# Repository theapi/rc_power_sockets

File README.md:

# RC Power Sockets
Using remote controlled power sockets - http://www.maplin.co.uk/p/remote-controlled-mains-sockets-set-3-pack-n79ka

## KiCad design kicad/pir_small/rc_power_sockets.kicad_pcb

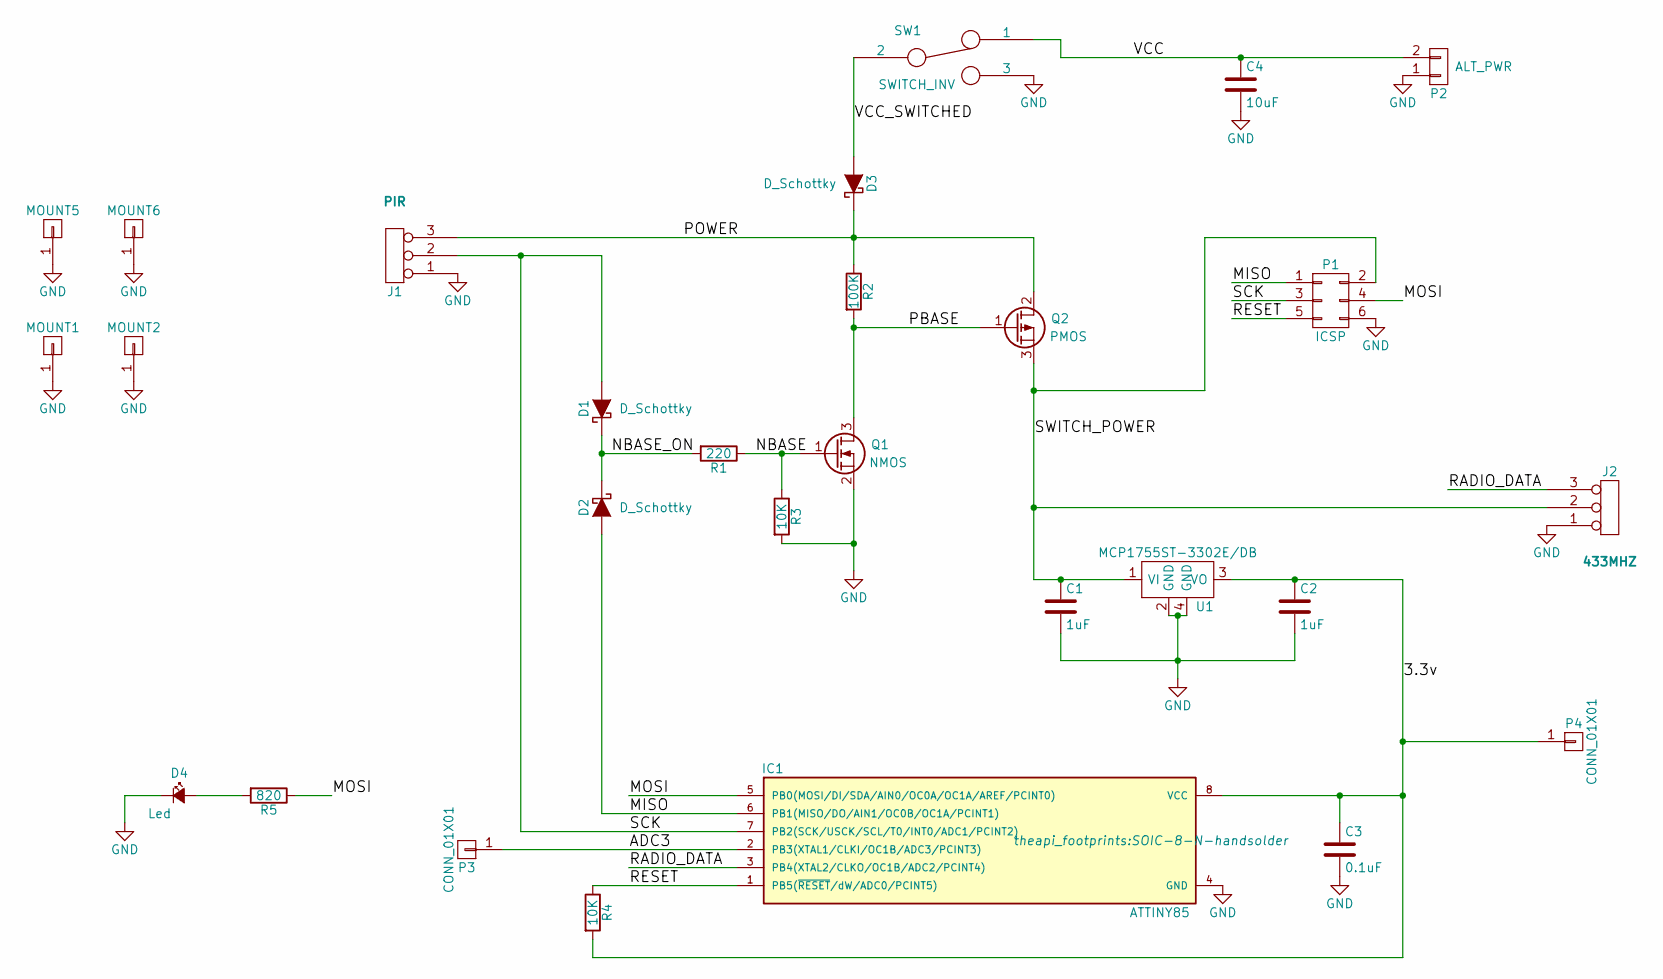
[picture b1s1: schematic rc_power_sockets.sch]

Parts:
C1, C2: 1uF; C_0805_HandSoldering
C3: 0.1uF; C_0805_HandSoldering
C4: 10uF; C_0805_HandSoldering
D1, D2, D3: D_Schottky; SOD-123-handsolder
D4: Led; LED_0805
IC1: ATTINY85; SOIC-8-N-handsolder
J1: PIR; Socket_Strip_Straight_1x03
J2: 433MHZ; Socket_Strip_Straight_1x03
MOUNT1, MOUNT2, MOUNT5, MOUNT6: CONN_01X01; Pin_Header_Straight_1x01
P1: ICSP; Pin_Header_Straight_2x03
P2: ALT_PWR; Pin_Header_Straight_1x02
P3, P4: CONN_01X01; Pin_Header_Straight_1x01
Q1: NMOS; SOT-23_Handsoldering
Q2: PMOS; SOT-23_Handsoldering
R1: 220; R_0805_HandSoldering
R2: 100K; R_0805_HandSoldering
R3, R4: 10K; R_0805_HandSoldering
R5: 820; R_0805_HandSoldering
SW1: SWITCH_INV; SW_Micro_SPST
U1: MCP1755ST-3302E/DB; SOT-223

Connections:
/3.3v: C2.1, C3.1, IC1.8 (VCC), P4.1, R4.2, U1.3 (VO)
/ADC3: IC1.2 (PB3(XTAL1/CLKI/OC1B/ADC3/PCINT3)), P3.1
/MISO: D2.2 (A), IC1.6 (PB1(MISO/DO/AIN1/OC0B/OC1A/PCINT1)), P1.1
/MOSI: IC1.5 (PB0(MOSI/DI/SDA/AIN0/OC0A/OC1A/AREF/PCI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), P1.4, R5.1
/NBASE: Q1.1 (G), R1.1, R3.1
/NBASE_ON: D1.1 (K), D2.1 (K), R1.2
/PBASE: Q1.3 (D), Q2.1 (G), R2.2
/POWER: D3.1 (K), J1.3, Q2.2 (D), R2.1
/RADIO_DATA: IC1.3 (PB4(XTAL2/CLKO/OC1B/ADC2/PCINT4)), J2.3
/RESET: IC1.1 (PB5(~RESET~/dW/ADC0/PCINT5)), P1.5, R4.1
/SCK: D1.2 (A), IC1.7 (PB2(SCK/USCK/SCL/T0/INT0/ADC1/PCINT2)), J1.2, P1.3
/SWITCH_POWER: C1.1, J2.2, P1.2, Q2.3 (S), U1.1 (VI)
/VCC: C4.1, P2.2, SW1.1
/VCC_SWITCHED: D3.2 (A), SW1.2
GND: C1.2, C2.2, C3.2, C4.2, D4.1 (K), IC1.4 (GND), J1.1, J2.1, MOUNT1.1, MOUNT2.1, MOUNT5.1, MOUNT6.1, P1.6, P2.1, Q1.2 (S), R3.2, SW1.3, U1.2 (GND), U1.4 (GND)
unnamed: D4.2 (A), R5.2

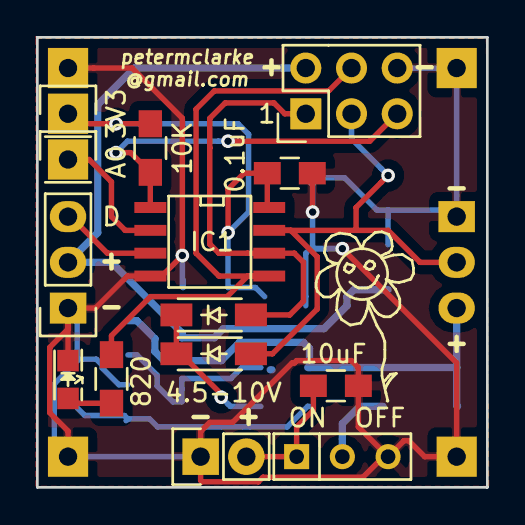
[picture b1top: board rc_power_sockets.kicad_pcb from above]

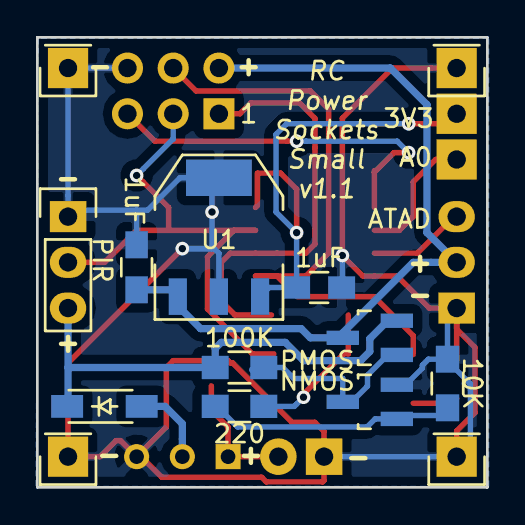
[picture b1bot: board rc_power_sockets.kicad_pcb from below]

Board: 2 copper layers, 25.0 x 25.0 mm, 28 parts (14 on the bottom side), 16 nets.

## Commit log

2016-02-03 Basic demo
2016-02-03 Working
2016-02-13 With motion sensor
2016-02-15 Only transmit a few times
2016-02-16 Self power off
2016-02-17 Changed pin assignments
2016-02-19 Sleep while in motion
2016-02-20 Sleep off for debugging
2016-02-20 Sleep enabled
2016-02-21 Debug on different pin
2016-02-21 Keep the switch on for 30 minutes
2016-02-21 Ignore motion interrupt if too soon
2016-02-22 No need for pin interrupt as timing is handled by watchdog
2016-02-22 Removed eroneous file
2016-02-23 Reset the ON timer on the rising edge of the motion detector
2016-02-23 Go back to sleep on motion wake up
2016-02-24 Reset timer on falling edge
2016-02-24 Stuck at 15 minutes
2016-02-25 Refactor
2016-02-25 35 minutes
2016-02-27 ATTINY85 support
2016-02-29 ATTiny85 pins
2016-02-29 Start of schematic
2016-03-01 Library
2016-03-02 Schematic
2016-03-03 SIL for sensors
2016-03-03 Annotate
2016-03-03 ATTiny85 sleep
2016-03-03 Footprints
2016-03-03 Initial pcb
2016-03-03 GND pin on header
2016-03-04 SMD ATTiny
2016-03-15 Use existing parts
2016-03-16 50mm x 50mm
2016-03-17 Layout
2016-03-19 Layout change
2016-03-20 Traces
2016-03-20 grounds
2016-03-21 Switched power plane
2016-03-21 Mounting holes
2016-03-21 Grounded mounting holes
2016-03-21 Labels on connectors
2016-03-21 Schematic update
2016-03-21 Moved silkscreens
2016-03-21 Wider VCC trace
2016-03-21 Logo
2016-03-22 M3 mounting holes
2016-03-22 Logo smaller
2016-03-22 Gerber files
2016-03-23 Reversed polarity protection
2016-03-23 Changed voltage regulator cap values
2016-03-23 Updated gerbers
2016-03-23 Changed voltage regulator to handle higher input
2016-03-24 Silkscreen update
2016-03-24 Gerber update
2016-03-24 oshpark pcb rules
2016-03-25 Positioned the PIR mounting
2016-03-25 Silkscreen changes
2016-03-25 Removed gerbers
2016-03-26 Redesign with CR2032
2016-03-26 Two cell batteries for 6V
2016-03-26 MCP1755S 3v3 voltage regulator
2016-03-26 Ground the 4th pin of the regulator
2016-03-26 Ground tidy
2016-03-27 Footprints & silkscreen tweaks
2016-03-27 Diode designators moved
2016-03-27 Alternative power input
2016-03-27 Gerbers & grounded pir holes
2016-03-27 Fixed missing connection
2016-03-27 Via tweaking
2016-03-27 Gerbers
2016-03-27 Tiny tweak on 3v trace
2016-03-28 Track & via sizes from Arduino Uno
2016-03-28 Via out annular ring to keep eurocircuits happy
2016-03-29 Arduino directory rename
2016-03-29 Kicad directory name
2016-03-29 Linux path
2016-03-29 Moved cap away from mounting hole
2016-03-30 20mm pin to pin for CR2032 holder
2016-03-30 Power switch
2016-03-30 Moved the led
2016-03-30 Moved components out of the way of parts on the PIR
2016-03-31 switch_power trace tweak
2016-03-31 Flipped the radio connector to the back
2016-04-03 Metric output
2016-04-03 File extension changes
2016-04-03 gerber zip
2016-04-03 Ordered at OSH Park
2016-04-05 100k pull up on the pmos
2016-04-22 Easier hand soldering
2016-04-28 One inch square
2016-04-28 Trace tweaks
2016-04-29 Silkscreen
2016-04-29 Gerber settings
2016-05-01 Changed layout
2016-05-02 Power pins
2016-05-03 Renders
2016-05-19 Corrected pchannel mosfet
2016-05-19 Less transmissions & ~15 minutes on time
2016-05-20 10uF cap on the power input
2016-08-28 Note to use https://github.com/SpenceKonde/ATTinyCore
2016-08-31 Corrected the PMOS
2016-08-31 Capacitor on the power input
2016-08-31 Tiny logo
2016-08-31 Gerbers for pcbs.io
2016-09-03 Images of v1.1
2016-09-05 Status indicator for external leds
2016-09-11 Mains powered version
2016-09-11 Handle the the motion sensor going high during transmission
2016-09-11 Simpler timing
2016-09-17 Faster response
